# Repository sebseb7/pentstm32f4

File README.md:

# PentSTM32f4 

a small template project to use with the stm32f4xx / stm32f2xx

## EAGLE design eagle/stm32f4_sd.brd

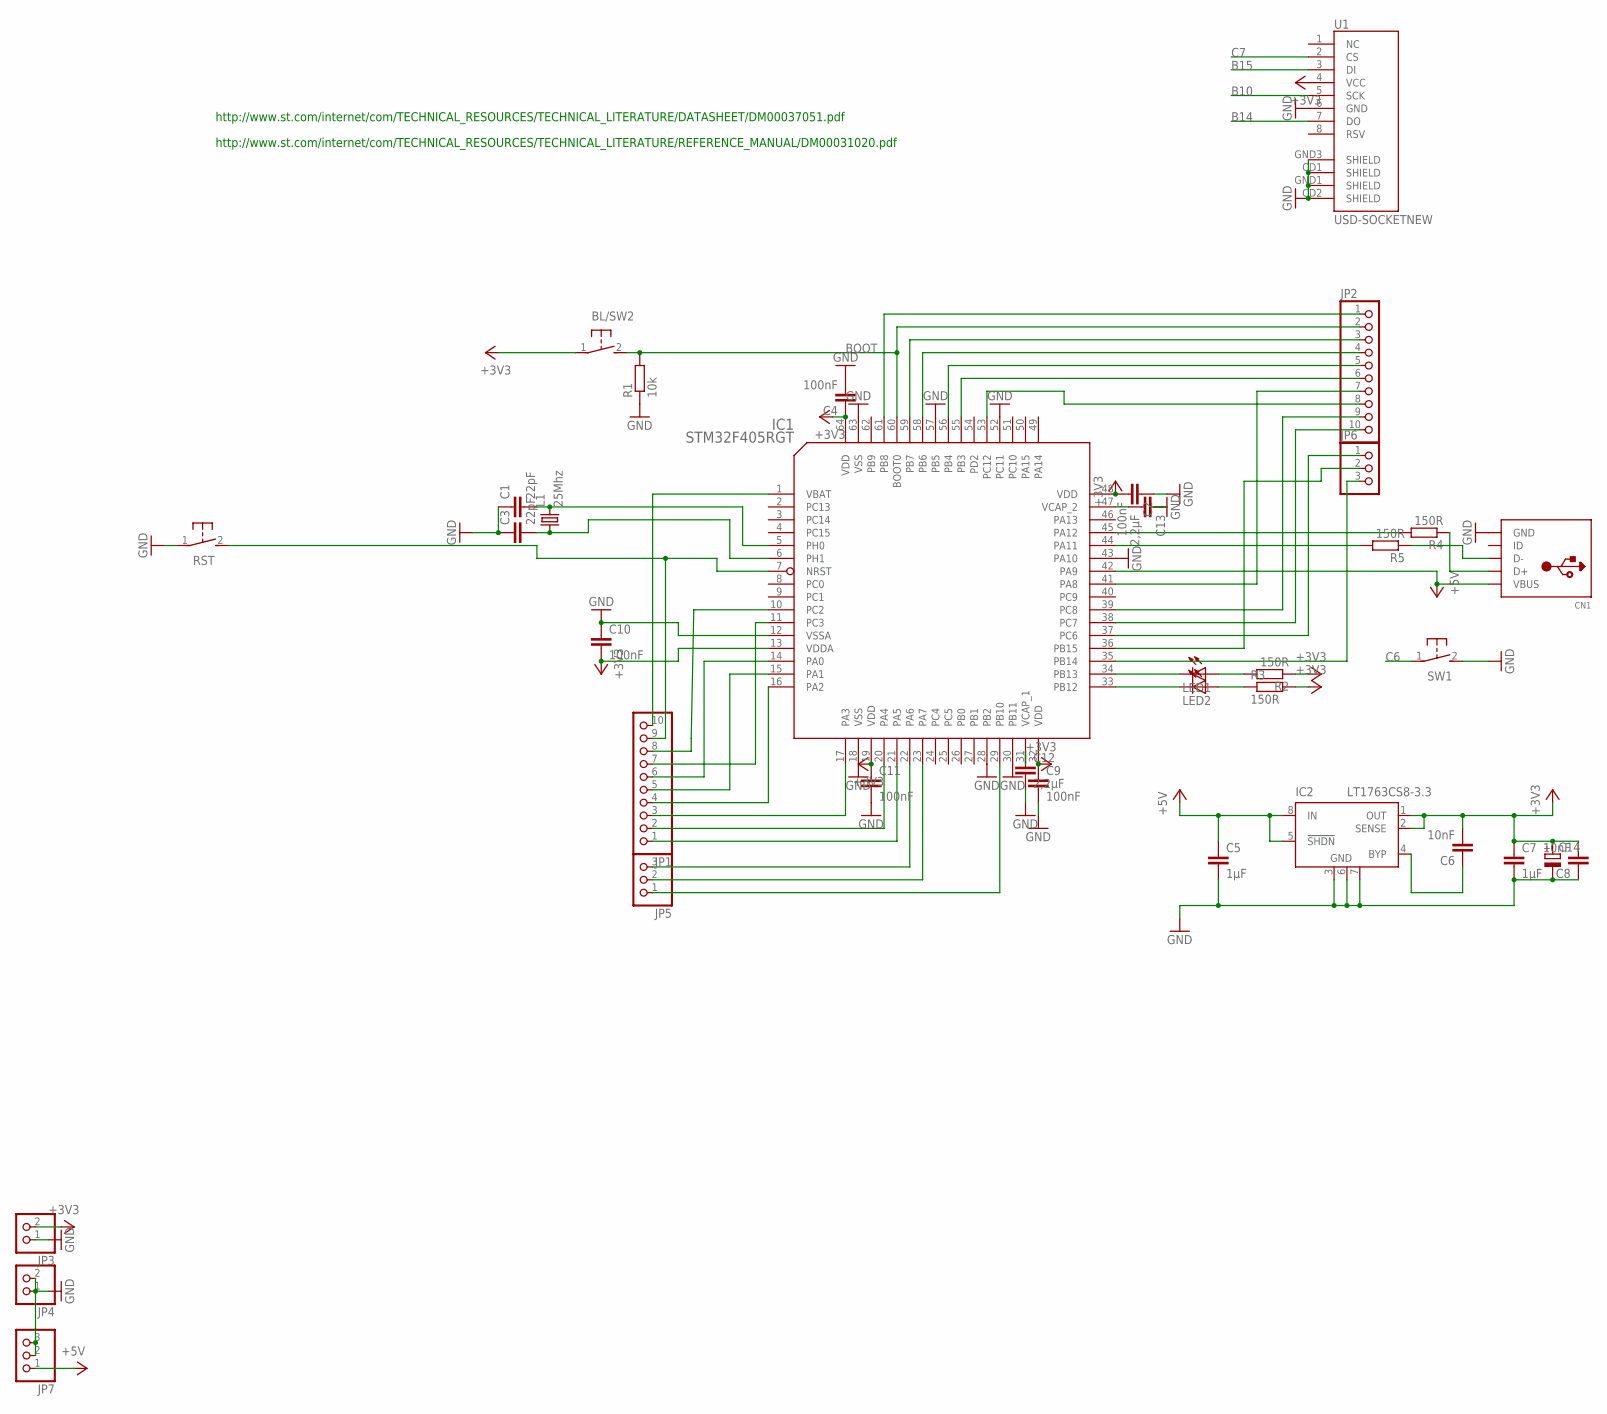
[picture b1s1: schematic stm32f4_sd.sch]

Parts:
BL/SW2: SWITCH_MCTAEF
C1, C3: 22pF; C0402
C2, C4, C9, C10, C11: 100nF; C0402
C5, C7: 1µF; 0805
C6, C8: 10nF; C0402
C12, C13: 2,2µF; 0805
C14: CPOL-EUSMCA; SMC_A
CN1: USBMINIB; USB-MINIB
IC1: STM32F405RGT; LQFP64
IC2: LT1763CS8-3.3; SOIC8
JP1, JP2: PINHD-1X10_2.54; 1X10
JP3, JP4: PINHD-1X02_2.54; 1X02
JP5, JP6, JP7: PINHD-1X03_2.54; 1X03
L1: 25Mhz; X22
LED1, LED2: LEDCHIPLED_0805; CHIPLED_0805
R1: 10k; R0402
R2, R3, R4, R5: 150R; R0402
RST: SWITCH_MCTAEF
SW1: SWITCH_MCTAEF
U1: USD-SOCKETNEW; MICRO-SD-SOCKET-PP

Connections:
+3V3: BL/SW2.1, C2.2, C4.1, C6.2, C7.1, C8.2, C9.1, C10.2, C11.1, C14.+, IC1.13 (VDDA), IC1.19 (VDD), IC1.32 (VDD), IC1.48 (VDD), IC1.64 (VDD), IC2.1 (OUT), IC2.2 (SENSE), JP3.2, R2.1, R3.2, U1.4 (VCC)
+5V: C5.1, CN1.VBUS, IC1.42 (PA9), IC2.5 (!SHDN), IC2.8 (IN), JP7.1
A0: IC1.14 (PA0), JP1.6
A1: IC1.15 (PA1), JP1.5
A3: IC1.17 (PA3), JP1.3
A4: IC1.20 (PA4), JP1.2
A5: IC1.21 (PA5), JP1.1
A6: IC1.22 (PA6), JP5.3
A7: IC1.23 (PA7), JP5.2
A8: IC1.41 (PA8), JP2.7
B4: IC1.56 (PB4), JP2.5
B6: IC1.58 (PB6), JP2.4
B7: IC1.59 (PB7), JP2.3
B8: IC1.61 (PB8), JP2.1
B10: IC1.29 (PB10), JP5.1, U1.5 (SCK)
B14: IC1.35 (PB14), JP6.3, U1.7 (DO)
B15: IC1.36 (PB15), JP6.2, U1.3 (DI)
BOOT: BL/SW2.2, IC1.60 (BOOT0), JP2.2, R1.2
C2: IC1.10 (PC2), JP1.8
C3: IC1.11 (PC3), JP1.7
C6: IC1.37 (PC6), JP6.1, SW1.1
C7: IC1.38 (PC7), JP2.10, U1.2 (CS)
C8: IC1.39 (PC8), JP2.9
C12: IC1.53 (PC12), JP2.8
GND: C1.1, C2.1, C3.1, C4.2, C5.2, C7.2, C8.1, C9.2, C10.1, C11.2, C12.2, C13.1, C14.-, CN1.GND, IC1.12 (VSSA), IC1.18 (VSS), IC1.28 (PB2), IC1.30 (PB11), IC1.43 (PA10), IC1.52 (PC11), IC1.57 (PB5), IC1.63 (VSS), IC2.3 (GND), IC2.6 (GND), IC2.7 (GND), JP3.1, JP4.1, JP4.2, JP7.2, JP7.3, R1.1, RST.1, SW1.2, U1.6 (GND), U1.CD1 (SHIELD), U1.CD2 (SHIELD), U1.GND1 (SHIELD), U1.GND3 (SHIELD)
unnamed: IC1.16 (PA2), JP1.4
unnamed: C3.2, IC1.6 (PH1), L1.1
unnamed: C1.2, IC1.5 (PH0), L1.3 (2)
unnamed: IC1.7 (NRST), JP1.9, RST.2
unnamed: IC1.44 (PA11), R5.2
unnamed: C12.1, IC1.31 (VCAP_1)
unnamed: C6.1, IC2.4 (BYP)
unnamed: C13.2, IC1.47 (VCAP_2)
unnamed: IC1.33 (PB12), LED2.C
unnamed: LED1.A, R2.2
unnamed: LED2.A, R3.1
unnamed: IC1.34 (PB13), LED1.C
unnamed: IC1.45 (PA12), R4.2
unnamed: CN1.D+, R4.1
unnamed: CN1.D-, R5.1
PB3: IC1.55 (PB3), JP2.6
VBAT: IC1.1 (VBAT), JP1.10

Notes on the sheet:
http://www.st.com/internet/com/TECHNICAL_RESOURCES/TECHNICAL_LITERATURE/REFERENCE_MANUAL/DM00031020.pdf
http://www.st.com/internet/com/TECHNICAL_RESOURCES/TECHNICAL_LITERATURE/DATASHEET/DM00037051.pdf

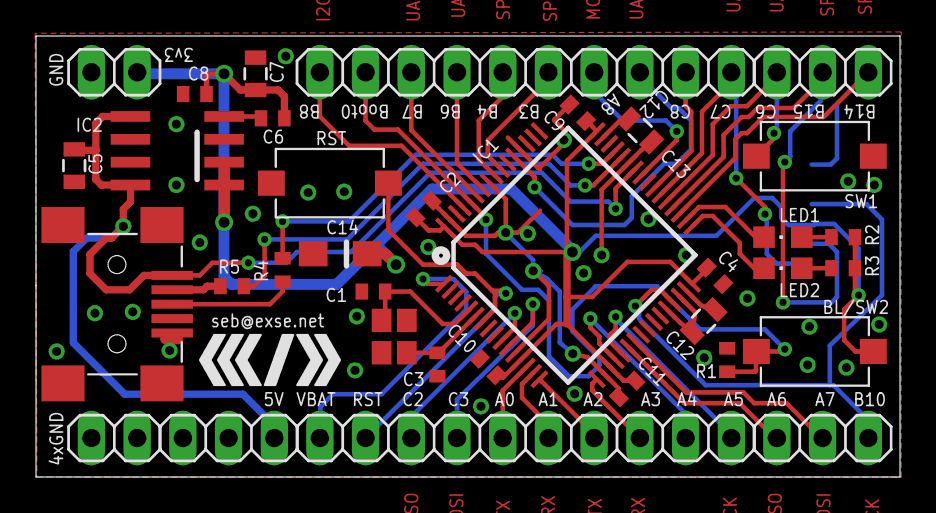
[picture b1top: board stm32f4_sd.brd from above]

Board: 2 copper layers, 48.0 x 24.5 mm, 36 parts (1 on the bottom side), 42 nets.

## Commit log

2012-09-25 init
2012-09-25 added usb drivers
2012-09-25 now 3mbit up+down work
2012-09-25 back to 12mhz
2012-09-26 reduced compiler warnings and other fixes
2012-09-26 typo
2012-09-26 fixed gc flags
2012-09-26 made make to print less
2012-09-28 makeit work in the discovery board
2012-09-28 send a byte via usb
2012-10-17 sdcard
2012-10-20 warning fix without fpu
2012-10-21 removed
2012-10-21 stm32f2 support
2012-10-21 noecho
2012-10-22 fat32 on sdcard via spi
2012-10-22 flag change
2012-10-22 flag changes
2012-10-22 added usbprintf()
2012-10-22 imu code
2012-10-22 mpu6050 driver
2012-10-22 added euler
2012-10-22 imu application
2012-10-22 stm32f2/stm32f4 compile fixes
2012-10-22 merge
2012-10-25 added f10x support and duplicates removed
2012-10-25 f1 drivers
2012-10-25 clean
2012-10-25 exposed i2c internals
2012-10-25 i2c rate
2012-10-25 transition fix
2012-10-25 imu code update
2012-10-25 non-usb compile fix (already in master)
2012-10-25 more f1 compile fixes
2013-01-07 eagle files
2013-01-19 pcb pic
2013-01-31 minor updates
